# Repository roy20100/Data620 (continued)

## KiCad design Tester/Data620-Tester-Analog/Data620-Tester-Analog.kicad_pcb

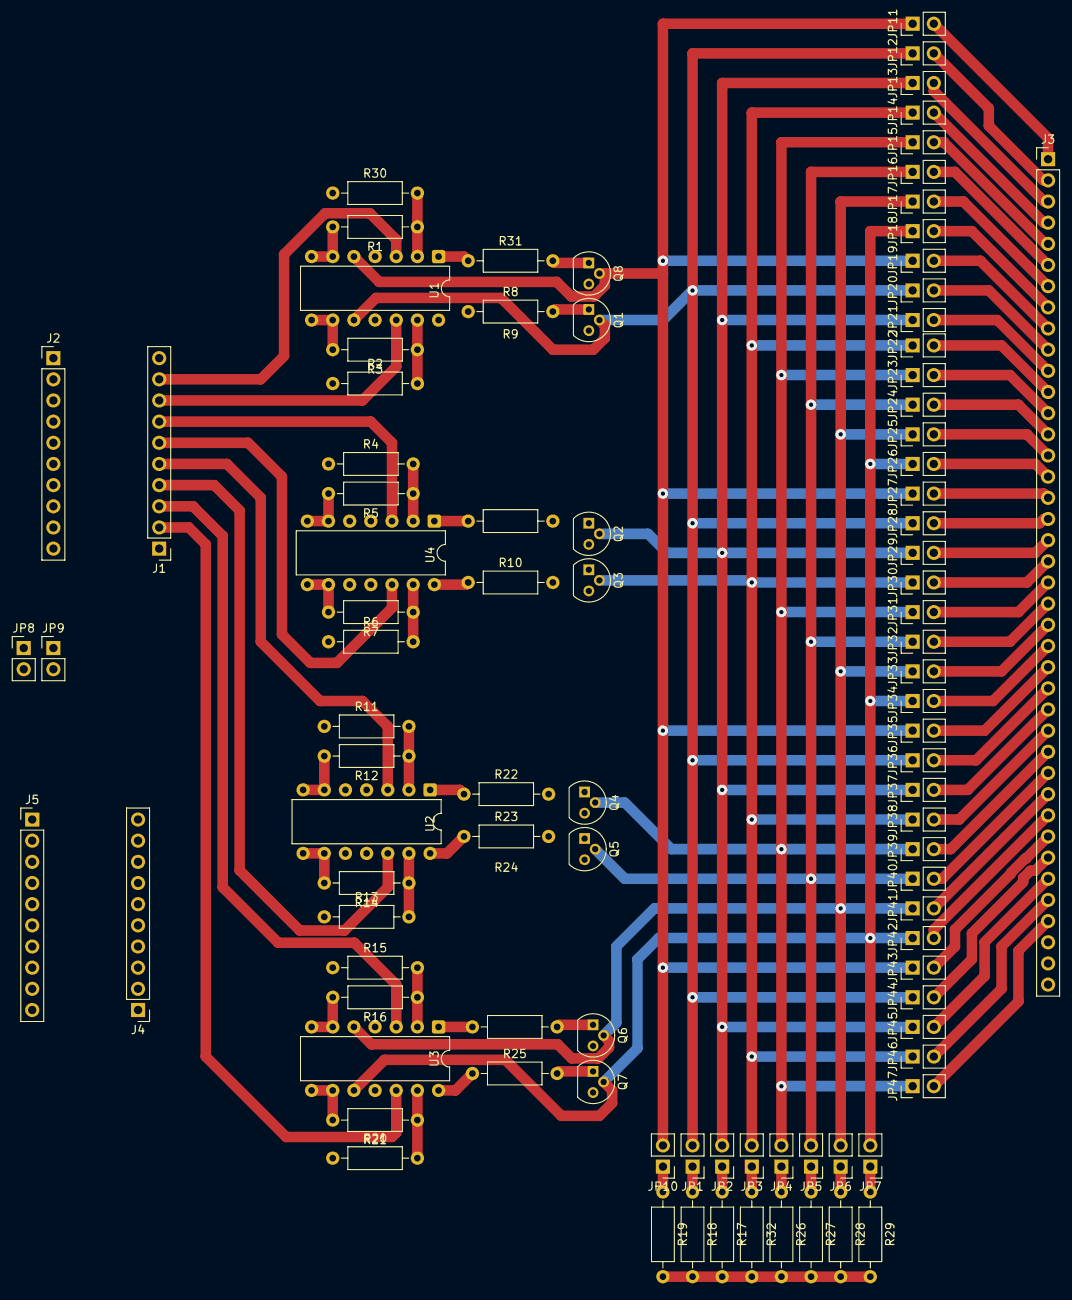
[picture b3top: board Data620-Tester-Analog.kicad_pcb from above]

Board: 2 copper layers, 96 parts (0 on the bottom side), 100 nets.

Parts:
J1: DAC6578_2; PinHeader_1x10_P2.54mm_Vertical
J2: ADS7830_1; PinHeader_1x10_P2.54mm_Vertical
J3: Conn_01x40; PinHeader_1x40_P2.54mm_Vertical
J4: ADS7830_2; PinHeader_1x10_P2.54mm_Vertical
J5: DAC6578_1; PinHeader_1x10_P2.54mm_Vertical
JP1, JP2, JP3, JP4, JP5, JP6, JP7, JP8, JP9, JP10, JP11, JP12, JP13, JP14, JP15, JP16, JP17, JP18, JP19, JP20, JP21, JP22, JP23, JP24, JP25, JP26, JP27, JP28, JP29, JP30, JP31, JP32, JP33, JP34, JP35, JP36, JP37, JP38, JP39, JP40, JP41, JP42, JP43, JP44, JP45, JP46, JP47: Jumper_2_Bridged; PinHeader_1x02_P2.54mm_Vertical
Q1, Q2, Q3, Q4, Q5, Q6, Q7, Q8: Q_NPN_BEC; TO-92
R1, R3, R5, R7, R12, R14, R16, R21: 10k; R_Axial_DIN0207_L6.3mm_D2.5mm_P10.16mm_Horizontal
R2, R4, R6, R11, R13, R15, R20, R30: 2.5k; R_Axial_DIN0207_L6.3mm_D2.5mm_P10.16mm_Horizontal
R8, R9, R10, R22, R23, R24, R25, R31: 499; R_Axial_DIN0207_L6.3mm_D2.5mm_P10.16mm_Horizontal
R17, R18, R19, R26, R27, R28, R29, R32: 2k; R_Axial_DIN0207_L6.3mm_D2.5mm_P10.16mm_Horizontal
U1, U2, U3, U4: TL084; DIP-14_W7.62mm

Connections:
+3.3V: J2.1, J5.3, R2.1, R4.1, R6.1, R11.1, R13.1, R15.1, R20.1, R30.1, U1.4 (V+), U2.4 (V+), U3.4 (V+), U4.4 (V+)
-12V: J3.40, R17.2, R18.2, R19.2, R26.2, R27.2, R28.2, R29.2, R32.2, U1.11 (V-), U2.11 (V-), U3.11 (V-), U4.11 (V-)
/ADC0: J4.3, R1.1, R30.2, U1.2 (-)
/ADC1: J4.4, R2.2, R3.1, U1.13 (-)
/ADC2: J4.5, R4.2, R5.1, U4.2 (-)
/ADC3: J4.6, R6.2, R7.1, U4.13 (-)
/ADC4: J4.7, R11.2, R12.1, U2.2 (-)
/ADC5: J4.8, R13.2, R14.1, U2.13 (-)
/ADC6: J4.9, R15.2, R16.1, U3.2 (-)
/ADC7: J4.10, R20.2, R21.1, U3.13 (-)
/DAC0: J1.9, U1.3 (+)
/DAC1: J1.8, U1.12 (+)
/DAC2: J1.7, U4.3 (+)
/DAC3: J1.6, U4.12 (+)
/DAC4: J1.5, U2.3 (+)
/DAC5: J1.4, U2.12 (+)
/DAC6: J1.3, U3.3 (+)
/DAC7: J1.2, U3.12 (+)
/IO0: JP10.2 (B), JP11.1 (A), JP19.1 (A), JP27.1 (A), JP35.1 (A), JP43.1 (A), Q8.2 (E), U1.5 (+)
/IO1: JP1.2 (B), JP12.1 (A), JP20.1 (A), JP28.1 (A), JP36.1 (A), JP44.1 (A), Q1.2 (E), U1.10 (+)
/IO2: JP2.2 (B), JP13.1 (A), JP21.1 (A), JP29.1 (A), JP37.1 (A), JP45.1 (A), Q2.2 (E), U4.5 (+)
/IO3: JP3.2 (B), JP14.1 (A), JP22.1 (A), JP30.1 (A), JP38.1 (A), JP46.1 (A), Q3.2 (E), U4.10 (+)
/IO4: JP4.2 (B), JP15.1 (A), JP23.1 (A), JP31.1 (A), JP39.1 (A), JP47.1 (A), Q4.2 (E), U2.5 (+)
/IO5: JP5.2 (B), JP16.1 (A), JP24.1 (A), JP32.1 (A), JP40.1 (A), Q5.2 (E), U2.10 (+)
/IO6: JP6.2 (B), JP17.1 (A), JP25.1 (A), JP33.1 (A), JP41.1 (A), Q6.2 (E), U3.5 (+)
/IO7: JP7.2 (B), JP18.1 (A), JP26.1 (A), JP34.1 (A), JP42.1 (A), Q7.2 (E), U3.10 (+)
/SCK1: J5.6, JP8.2 (B)
/SCK2: J2.3, JP8.1 (A)
/SDA1: J5.5, JP9.2 (B)
/SDA2: J2.4, JP9.1 (A)
GND: J1.1, J2.2, J3.38, J5.4, Q1.3 (C), Q2.3 (C), Q3.3 (C), Q4.3 (C), Q5.3 (C), Q6.3 (C), Q7.3 (C), Q8.3 (C)
unnamed: J3.1, JP11.2 (B)
unnamed: J3.2, JP12.2 (B)
unnamed: J3.3, JP13.2 (B)
unnamed: J3.4, JP14.2 (B)
unnamed: J3.5, JP15.2 (B)
unnamed: J3.6, JP16.2 (B)
unnamed: J3.7, JP17.2 (B)
unnamed: J3.8, JP18.2 (B)
unnamed: J3.9, JP19.2 (B)
unnamed: J3.10, JP20.2 (B)
unnamed: J3.11, JP21.2 (B)
unnamed: J3.12, JP22.2 (B)
unnamed: J3.13, JP23.2 (B)
unnamed: J3.14, JP24.2 (B)
unnamed: J3.15, JP25.2 (B)
unnamed: J3.16, JP26.2 (B)
unnamed: J3.17, JP27.2 (B)
unnamed: J3.18, JP28.2 (B)
unnamed: J3.19, JP29.2 (B)
unnamed: J3.20, JP30.2 (B)
unnamed: J3.21, JP31.2 (B)
unnamed: J3.22, JP32.2 (B)
unnamed: J3.23, JP33.2 (B)
unnamed: J3.24, JP34.2 (B)
unnamed: J3.25, JP35.2 (B)
unnamed: J3.26, JP36.2 (B)
unnamed: J3.27, JP37.2 (B)
unnamed: J3.28, JP38.2 (B)
unnamed: J3.29, JP39.2 (B)
unnamed: J3.30, JP40.2 (B)
unnamed: J3.31, JP41.2 (B)
unnamed: J3.32, JP42.2 (B)
unnamed: J3.33, JP43.2 (B)
unnamed: J3.34, JP44.2 (B)
unnamed: J3.35, JP45.2 (B)
unnamed: J3.36, JP46.2 (B)
unnamed: J3.37, JP47.2 (B)
unnamed: JP1.1 (A), R18.1
unnamed: JP2.1 (A), R17.1
unnamed: JP3.1 (A), R32.1
unnamed: JP4.1 (A), R26.1
unnamed: JP5.1 (A), R27.1
unnamed: JP6.1 (A), R28.1
unnamed: JP7.1 (A), R29.1
unnamed: JP10.1 (A), R19.1
unnamed: Q1.1 (B), R8.2
unnamed: Q2.1 (B), R9.2
unnamed: Q3.1 (B), R10.2
unnamed: Q4.1 (B), R22.2
unnamed: Q5.1 (B), R23.2
unnamed: Q6.1 (B), R24.2
unnamed: Q7.1 (B), R25.2
unnamed: Q8.1 (B), R31.2
unnamed: R8.1, U1.14
unnamed: R9.1, U4.1
unnamed: R10.1, U4.14
unnamed: R22.1, U2.1
unnamed: R23.1, U2.14
unnamed: R24.1, U3.1
unnamed: R25.1, U3.14
unnamed: R31.1, U1.1
unnamed: R1.2, U1.6 (-), U1.7
unnamed: R3.2, U1.8, U1.9 (-)
unnamed: R12.2, U2.6 (-), U2.7
unnamed: R14.2, U2.8, U2.9 (-)
unnamed: R16.2, U3.6 (-), U3.7
unnamed: R21.2, U3.8, U3.9 (-)
unnamed: R5.2, U4.6 (-), U4.7
unnamed: R7.2, U4.8, U4.9 (-)

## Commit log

2025-07-29 2025/7/28
2025-07-30 Added my notes on bruce273's reverse Engineered version of the REC04 PCB and an analog way to test the cards 8 lines at a time
2025-07-30 Collector side of ARI01 Q19, and corrected some zener diodes
2025-07-30 Most of Q15-19 reverse engineering done
2025-07-30 Reverted accidental settings changes
2025-07-30 2025/7/30
2025-07-30 Fixed fixed shape of the independent Flip-Flop in REC04
2025-07-30 before renumbering commit
2025-07-31 Complete renumbering and reordering of the schematic and PCB
2025-07-31 Traced Q21-24 area and -1V rail
2025-07-31 Reformed Schematic to A3 size and removed bus lines
2025-07-31 Replaced connector for the standard connector and created a PCB part for the 40 pin ELCO like connector
2025-07-31 2025/7/31
2025-08-01 2025/8/1
2025-08-02 First full pass of PA24, plus fixed background of my tested png
2025-08-02 Circuit RE complete, probably
2025-08-02 Added a missing cap to ARI01 and RE of ARI02
2025-08-02 Fixed an error in carry logic of ARI01, and drew up a logisim functional model
2025-08-02 2025/8/2
2025-08-02 fixed wrong internal power rail from -3.3 to -9V. rearranged pass PNP transistor
2025-08-02 fixed minor bugs and diode choices in PA24 and updloaded almost final PA24-1. still needs to change resistor values for PA24-1
2025-08-03 Updated resistor values in PA24-1 as they are smaller than PA24
2025-08-03 Add completed files for FF34
2025-08-03 up to date versions of PA24 and PA24-1
2025-08-03 2025/8/3
2025-08-03 Added Digital tester option Kicad
2025-08-03 fixed error in kicad design
2025-08-03 Added PA24-2 work in progress. resistance revision needs to be done. possibly the second transistor is PNP here
2025-08-03 Revised resistor values and added images for PA24-2
2025-08-03 PA24-2 schematic and PCB
2025-08-04 Finished Reverse Engineering TI01 Pack
2025-08-04 Added TI01 pdf
2025-08-04 GR26-1 Almost done
2025-08-04 PA26-1 Schematic and PCB
2025-08-04 Completed GR26-1
2025-08-04 2025/8/4
2025-08-05 Created XC31 PCB and corrected R63 to +6V instead of GND
2025-08-06 added misc files for testing
2025-08-06 2025/8/5
2025-08-15 first patch before PCB
2025-08-17 PCB of ARI01 done. Needs to be verified
